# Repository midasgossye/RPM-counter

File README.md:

# RPM counter

## Repo structure

* [**Electronics:**](https://github.com/midasgossye/RPM-counter/tree/main/Electronics) Contains everything related to the Electronics, this includes the schematic (in pdf), KiCad files (schematic & PCB layout), PCB gerber files and a BOM (Bill Of Materials)
* [**Programming:**](https://github.com/midasgossye/RPM-counter/tree/main/Programming) Contains the Arduino source code
* [**CAD:**](https://github.com/midasgossye/RPM-counter/tree/main/CAD) Contains the 3D design files (Solidworks & STEP format) and STL files for 3D printing of the case
* [**images:**](https://github.com/midasgossye/RPM-counter/tree/main/images) Images of RPM counter

## Acknowledgements:

This project is mainly based on GreatScott's DIY RPM meter. Check out his awesome video where he explains the design process and working details of his DIY RPM meter/tachometer based on a cheap IR distance sensor module: [youtu.be/6QZMt4yyylU](https://youtu.be/6QZMt4yyylU)

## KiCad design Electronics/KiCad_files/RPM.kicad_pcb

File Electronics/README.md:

# RPM counter Electronics

This folder contains the schematic, BOM, KiCad files and gerber fabrication files for the PCB.

## Main features:

* ATMEGA328P Microcontroller with Arduino bootloader
* Built-in CH340 based USB <-> Serial
* Constant current IR LED driver
* Runs on single-cell LiPo
  * TP4560 based LiPo battery charger
  * LiPo protection circuitry
  * 3.3 V -> 5 V boost converter

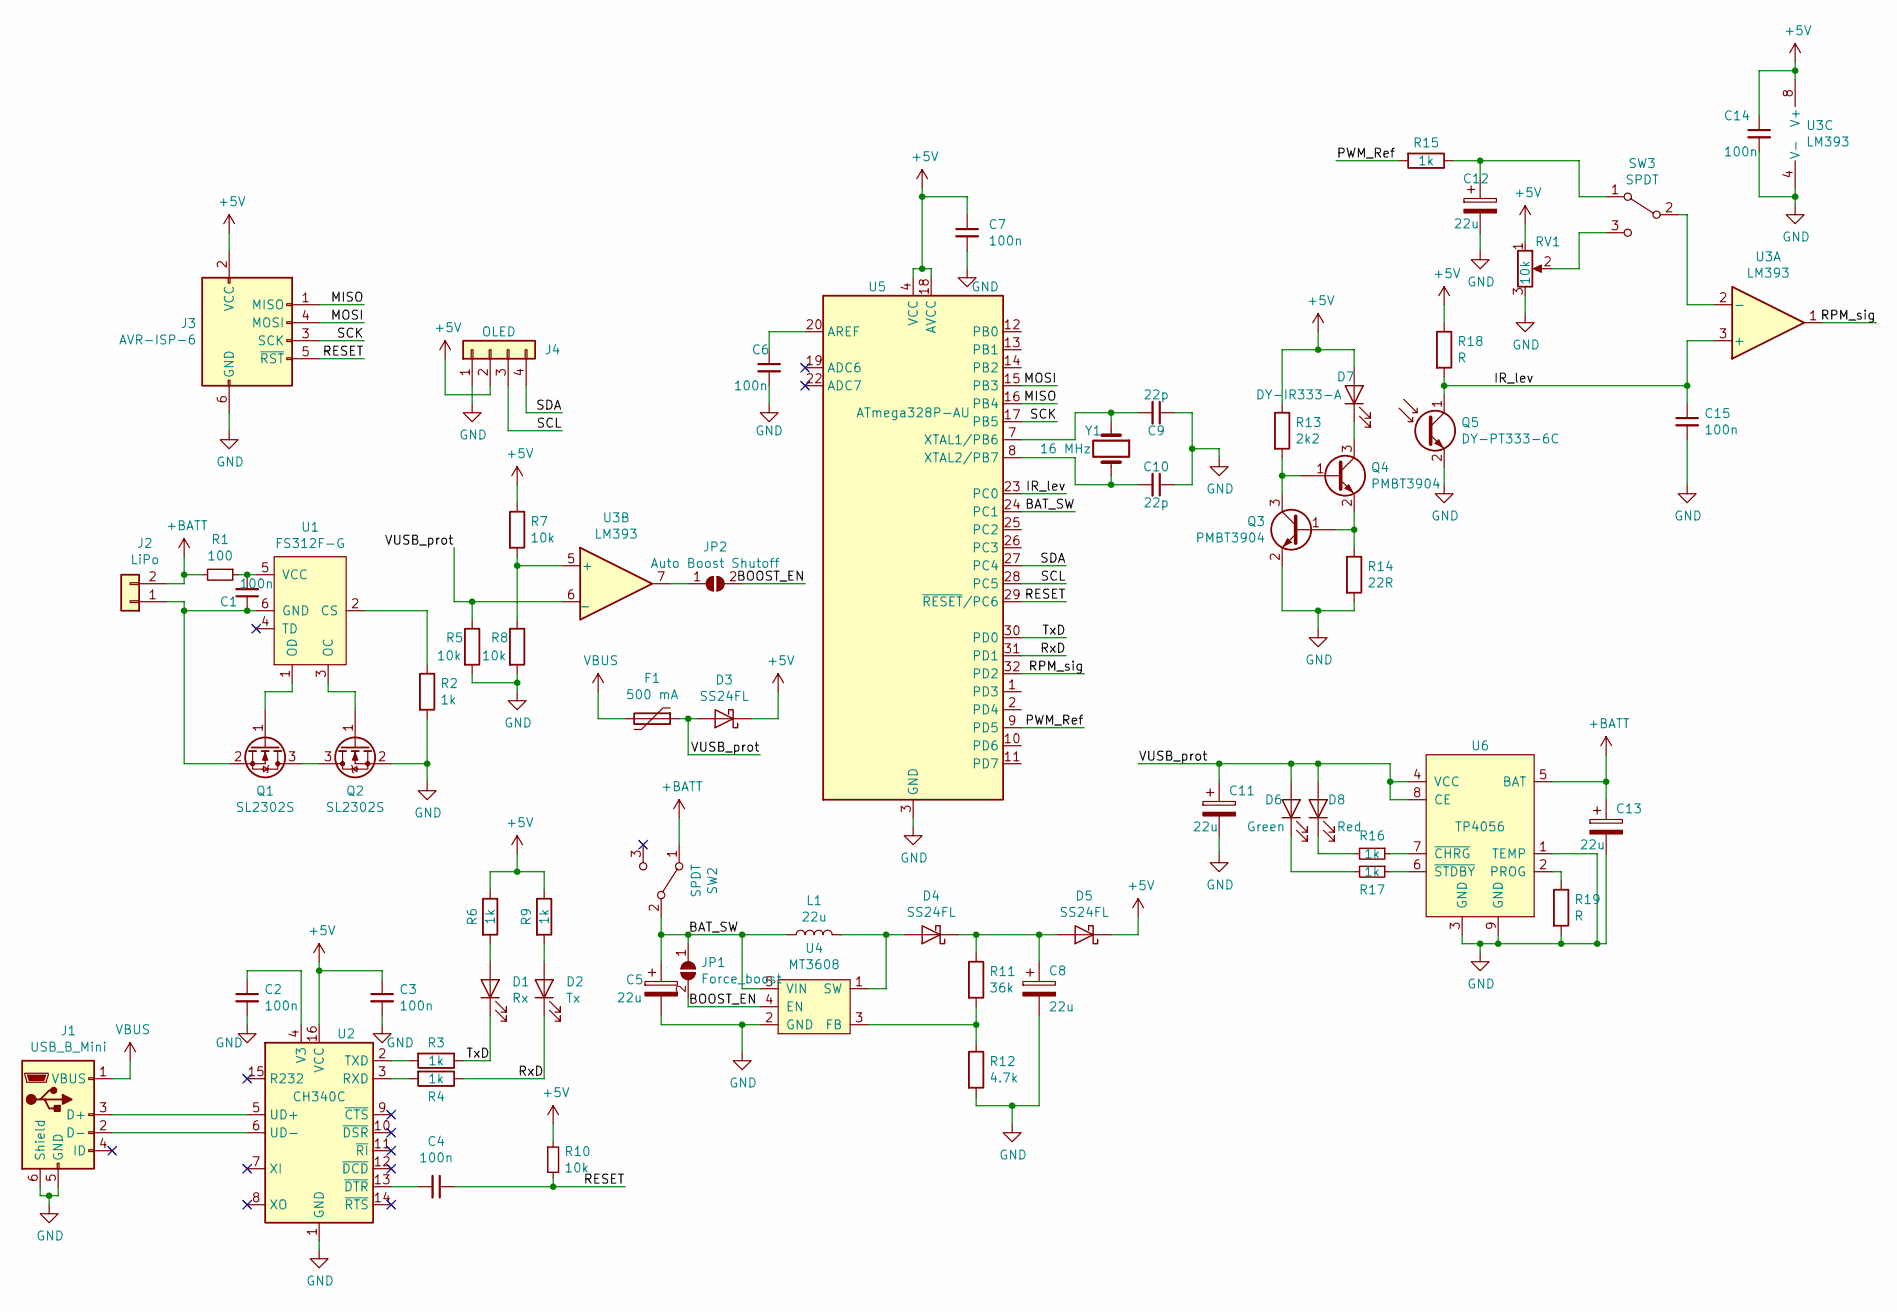
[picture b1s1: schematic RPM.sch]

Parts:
C1, C2, C3, C4, C6, C7, C14, C15: 100n; C_0603_1608Metric; MFR PART# 0603B104M250
C5, C8, C11, C12, C13: 22u; C_1206_3216Metric; MFR PART# CL31A226KOHNNNE
C9, C10: 22p; C_0805_2012Metric
D1: Rx; LED_0805_2012Metric
D2: Tx; LED_0805_2012Metric
D3, D4, D5: SS24FL; D_SOD-123; MFR PART# SS24FL
D6: Green; LED_0805_2012Metric
D7: DY-IR333-A; LED_D5.0mm_Horizontal_O1.27mm_Z3.0mm_IRGrey; MFR PART# DY-IR333-A
D8: Red; LED_0805_2012Metric
F1: 500 mA; Fuse_0805_2012Metric; MFR PART# JK-SMD0805-020
J1: USB_B_Mini; C105424; MFR PART# C105424
J2: LiPo; JST_PH_B2B-PH-K_1x02_P2.00mm_Vertical
J3: AVR-ISP-6; PinHeader_2x03_P2.54mm_Vertical; MFR PART# 210-92-03GB01
J4: OLED; PinSocket_1x04_P2.54mm_Vertical
JP1: Force_boost; SolderJumper-2_P1.3mm_Open_RoundedPad1.0x1.5mm
JP2: Auto Boost Shutoff; SolderJumper-2_P1.3mm_Open_RoundedPad1.0x1.5mm
L1: 22u; SNR5040K-SERIES; MFR PART# SNR5040K-220M
Q1, Q2: SL2302S; SOT-23; MFR PART# SL2302S
Q3, Q4: PMBT3904; SOT-23; MFR PART# PMBT3904,215
Q5: DY-PT333-6C; LED_D5.0mm_Horizontal_O1.27mm_Z3.0mm_Clear; MFR PART# DY-PT333-6C
R1: 100; R_0805_2012Metric
R2, R3, R4, R6, R9, R15, R16, R17: 1k; R_0603_1608Metric; MFR PART# 0603WAF1001T5E
R5, R7, R8, R10: 10k; R_0603_1608Metric; MFR PART# RTT03103JTP
R11: 36k; R_0603_1608Metric
R12: 4.7k; R_0603_1608Metric
R13: 2k2; R_0805_2012Metric
R14: 22R; R_Axial_DIN0207_L6.3mm_D2.5mm_P10.16mm_Horizontal; MFR PART# MFR0W4F390JA50
R18, R19: R; R_0805_2012Metric
RV1: 10k; Potentiometer_Vishay_T73XX_Horizontal; MFR PART# 3362S-1-103
SW2, SW3: SPDT; SK12D07VG5; MFR PART# SK12D07VG5
U1: FS312F-G; SOT-23-6; MFR PART# FS312F-G
U2: CH340C; SOIC-16_3.9x9.9mm_P1.27mm; MFR PART# CH340C
U3: LM393; SOP-8_3.76x4.96mm_P1.27mm; MFR PART# LM393
U4: MT3608; SOT-23-6; MFR PART# MT3608
U5: ATmega328P-AU; TQFP-32_7x7mm_P0.8mm; MFR PART# ATMEGA328P-AU
U6: TP4056; TI_SO-PowerPAD-8_ThermalVias; MFR PART# TP4056
Y1: 16 MHz; Crystal_HC18-U_Vertical; MFR PART# X49SD16MSD2SC

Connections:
+5V: C3.1, C7.1, C14.1, D3.1 (K), D5.1 (K), D7.2 (A), J3.2 (VCC), J4.2, R6.1, R7.1, R9.1, R10.1, R13.1, R18.1, RV1.1, U2.16 (VCC), U3.8 (V+), U5.4 (VCC), U5.6 (VCC), U5.18 (AVCC)
+BATT: C13.1, J2.2, R1.2, SW2.1 (A), U6.5 (BAT)
/BAT_SW: C5.1, JP1.1 (A), L1.1, SW2.2 (B), U4.5 (VIN), U5.24 (PC1)
/BOOST_EN: JP1.2 (B), JP2.2 (B), U4.4 (EN)
/IR_lev: C15.1, Q5.1 (C), R18.2, U3.3 (+), U5.23 (PC0)
/MISO: J3.1 (MISO), U5.16 (PB4)
/MOSI: J3.4 (MOSI), U5.15 (PB3)
/PWM_Ref: R15.2, U5.9 (PD5)
/RESET: C4.1, J3.5 (~RST), R10.2, U5.29 (~RESET~/PC6)
/RPM_sig: U3.1, U5.32 (PD2)
/RxD: D2.1 (K), R4.1, U5.31 (PD1)
/SCK: J3.3 (SCK), U5.17 (PB5)
/SCL: J4.3, U5.28 (PC5)
/SDA: J4.4, U5.27 (PC4)
/TxD: D1.1 (K), R3.1, U5.30 (PD0)
/VUSB_prot: C11.1, D3.2 (A), D6.2 (A), D8.2 (A), F1.1, R5.1, U3.6 (_), U6.4 (VCC), U6.8 (CE)
GND: C2.2, C3.2, C5.2, C6.2, C7.2, C8.2, C9.1, C10.1, C11.2, C12.2, C13.2, C14.2, C15.2, J1.5 (GND), J1.6 (Shield), J3.6 (GND), J4.1, Q2.2 (S), Q3.2 (E), Q5.2 (E), R2.2, R5.2, R8.2, R12.2, R14.2, R19.2, RV1.3, U2.1 (GND), U3.4 (V-), U4.2 (GND), U5.3 (GND), U5.5 (GND), U5.21 (GND), U6.1 (TEMP), U6.3 (GND), U6.9 (GND)
unnamed: C1.1, J2.1, Q1.2 (S), U1.6 (GND)
unnamed: C1.2, R1.1, U1.5 (VCC)
unnamed: C2.1, U2.4 (V3)
unnamed: C4.2, U2.13 (~DTR)
unnamed: C6.1, U5.20 (AREF)
unnamed: C8.1, D4.1 (K), D5.2 (A), R11.1
unnamed: C9.2, U5.7 (XTAL1/PB6), Y1.1
unnamed: C10.2, U5.8 (XTAL2/PB7), Y1.2
unnamed: C12.1, R15.1, SW3.1 (A)
unnamed: D1.2 (A), R6.2
unnamed: D2.2 (A), R9.2
unnamed: D4.2 (A), L1.2, U4.1 (SW)
unnamed: D6.1 (K), R17.2
unnamed: D7.1 (K), Q4.3 (C)
unnamed: D8.1 (K), R16.2
unnamed: J1.2 (D-), U2.6 (UD-)
unnamed: J1.3 (D+), U2.5 (UD+)
unnamed: JP2.1 (A), U3.7
unnamed: Q1.1 (G), U1.1 (OD)
unnamed: Q1.3 (D), Q2.3 (D)
unnamed: Q2.1 (G), U1.3 (OC)
unnamed: Q3.1 (B), Q4.2 (E), R14.1
unnamed: Q3.3 (C), Q4.1 (B), R13.2
unnamed: R2.1, U1.2 (CS)
unnamed: R3.2, U2.2 (TXD)
unnamed: R4.2, U2.3 (RXD)
unnamed: R7.2, R8.1, U3.5 (+)
unnamed: R11.2, R12.1, U4.3 (FB)
unnamed: R16.1, U6.7 (~CHRG)
unnamed: R17.1, U6.6 (~STDBY)
unnamed: R19.1, U6.2 (PROG)
unnamed: RV1.2, SW3.3 (C)
unnamed: SW3.2 (B), U3.2 (-)
VBUS: F1.2, J1.1 (VBUS)

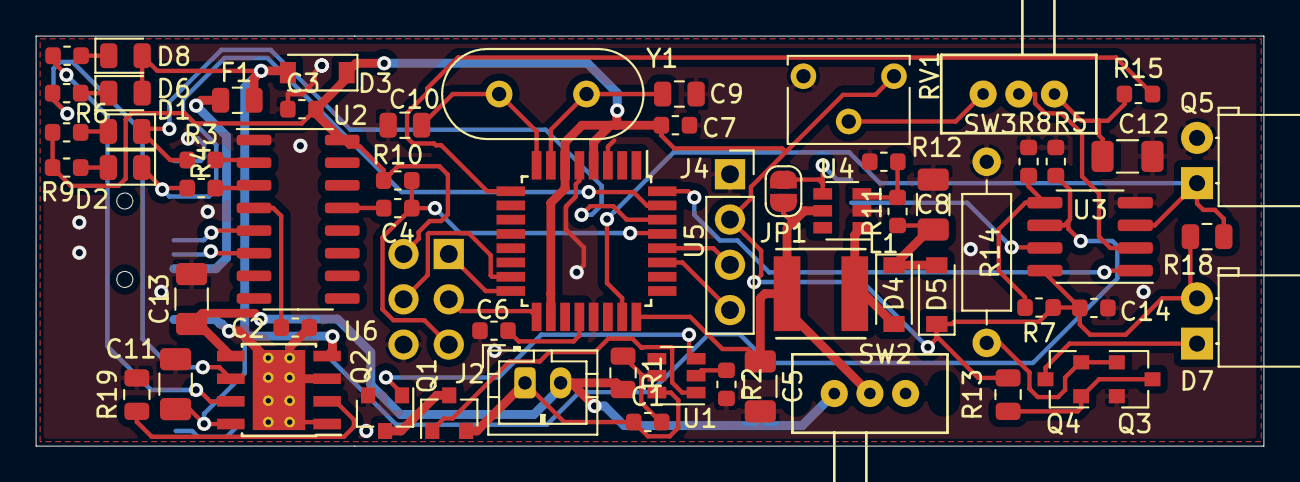
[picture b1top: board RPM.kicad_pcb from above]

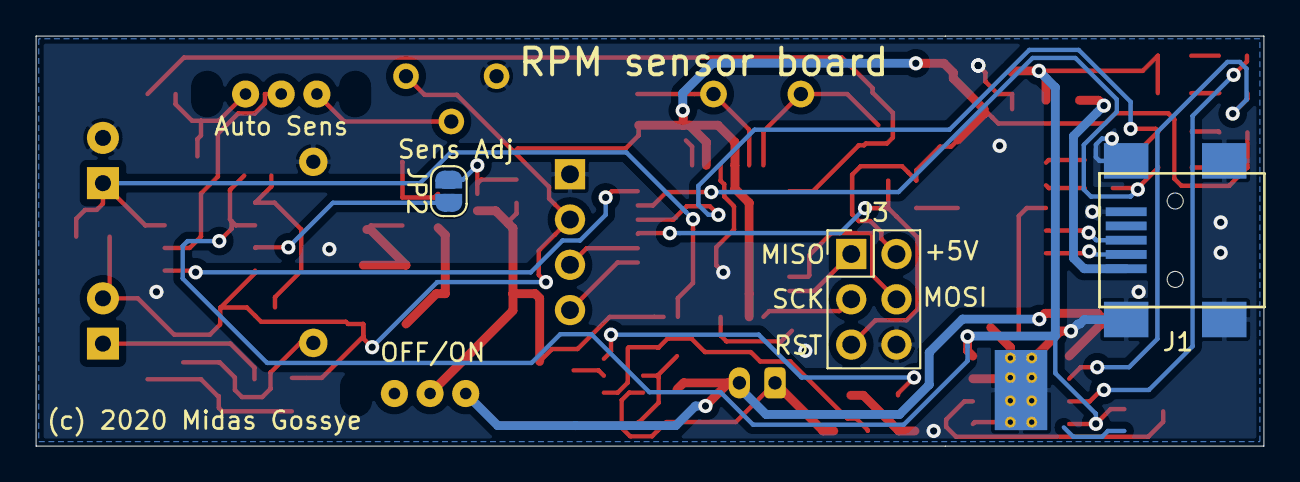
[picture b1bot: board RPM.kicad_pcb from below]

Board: 2 copper layers, 68.9 x 23.0 mm, 64 parts (3 on the bottom side), 51 nets.

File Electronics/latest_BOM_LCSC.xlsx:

Item | Qty | Reference(s) | Value | LibPart | Footprint | MFR PART#
1 | 7 | C1, C2, C3, C4, C6, C7, C14 | 100n | Device:C_Small | Capacitor_SMD:C_0603_1608Metric | 0603B104M250
2 | 5 | C5, C8, C11, C12, C13 | 22u | Device:CP | Capacitor_SMD:C_1206_3216Metric | CL31A226KOHNNNE
3 | 2 | C9, C10 | 22p | Device:C_Small | Capacitor_SMD:C_0805_2012Metric
4 | 1 | D1 | Rx | Device:LED | LED_SMD:LED_0805_2012Metric
5 | 1 | D2 | Tx | Device:LED | LED_SMD:LED_0805_2012Metric
6 | 3 | D3, D4, D5 | SS24FL | Device:D_Schottky | Diode_SMD:D_SOD-123 | SS24FL
7 | 1 | D6 | Green | Device:LED | LED_SMD:LED_0805_2012Metric
8 | 1 | D7 | DY-IR333-A | Device:LED | LED_THT:LED_D5.0mm_Horizontal_O1.27mm_Z3.0mm_IRGrey | DY-IR333-A
9 | 1 | D8 | Red | Device:LED | LED_SMD:LED_0805_2012Metric
10 | 1 | F1 | 500 mA | Device:Polyfuse | Fuse:Fuse_0805_2012Metric | JK-SMD0805-020
11 | 1 | J1 | USB_B_Mini | Connector:USB_B_Mini | SMD_connectors:C105424 | C105424
12 | 1 | J2 | LiPo | Connector_Generic:Conn_01x02 | Connector_JST:JST_PH_B2B-PH-K_1x02_P2.00mm_Vertical
13 | 1 | J3 | AVR-ISP-6 | Connector:AVR-ISP-6 | Connector_PinHeader_2.54mm:PinHeader_2x03_P2.54mm_Vertical | 210-92-03GB01
14 | 1 | J4 | OLED | Connector_Generic:Conn_01x04 | Connector_PinSocket_2.54mm:PinSocket_1x04_P2.54mm_Vertical
15 | 1 | JP1 | Force_boost | Jumper:SolderJumper_2_Open | Jumper:SolderJumper-2_P1.3mm_Open_RoundedPad1.0x1.5mm
16 | 1 | JP2 | Auto Boost Shutoff | Jumper:SolderJumper_2_Open | Jumper:SolderJumper-2_P1.3mm_Open_RoundedPad1.0x1.5mm
17 | 1 | L1 | 22u | Device:L | SMD_inductors:SNR5040K-SERIES | SNR5040K-220M
18 | 2 | Q1, Q2 | SL2302S | Device:Q_NMOS_GSD | Package_TO_SOT_SMD:SOT-23 | SL2302S
19 | 2 | Q3, Q4 | PMBT3904 | Device:Q_NPN_BEC | Package_TO_SOT_SMD:SOT-23 | PMBT3904,215
20 | 1 | Q5 | DY-PT333-6C | Device:Q_Photo_NPN_CE | LED_THT:LED_D5.0mm_Horizontal_O1.27mm_Z3.0mm_Clear | DY-PT333-6C
21 | 1 | R1 | 100 | Device:R_Small | Resistor_SMD:R_0805_2012Metric
22 | 6 | R2, R3, R4, R6, R9, R15 | 1k | Device:R | Resistor_SMD:R_0603_1608Metric | 0603WAF1001T5E
23 | 3 | R5, R7, R8 | 10k | Device:R | Resistor_SMD:R_0603_1608Metric
24 | 1 | R10 | 10k | Device:R_Small | Resistor_SMD:R_0603_1608Metric
25 | 1 | R11 | 36k | Device:R | Resistor_SMD:R_0603_1608Metric
26 | 1 | R12 | 4.7k | Device:R | Resistor_SMD:R_0603_1608Metric
27 | 1 | R13 | 2k2 | Device:R | Resistor_SMD:R_0805_2012Metric
28 | 1 | R14 | 39R | Device:R | Resistor_THT:R_Axial_DIN0207_L6.3mm_D2.5mm_P10.16mm_Horizontal | MFR0W4F390JA50
29 | 2 | R16, R17 | 1k | Device:R_Small | Resistor_SMD:R_0603_1608Metric | 0603WAF1001T5E
30 | 2 | R18, R19 | R | Device:R | Resistor_SMD:R_0805_2012Metric
31 | 1 | RV1 | 10k | Device:R_POT | Potentiometer_THT:Potentiometer_Vishay_T73XX_Horizontal | 3362S-1-103
32 | 2 | SW2, SW3 | SPDT | Switch:SW_SPDT | SMD_switches:SK12D07VG5 | SK12D07VG5
33 | 1 | U1 | FS312F-G | Battery_charger:FS312F-G | Package_TO_SOT_SMD:SOT-23-6 | FS312F-G
34 | 1 | U2 | CH340C | Interface_USB:CH340G | Package_SO:SOIC-16_3.9x9.9mm_P1.27mm | CH340C
35 | 1 | U3 | LM393 | Comparator:LM393 | Package_SO:SOP-8_3.76x4.96mm_P1.27mm | LM393
36 | 1 | U4 | MT3608 | Boost_converter:MT3608 | Package_TO_SOT_SMD:SOT-23-6 | MT3608
37 | 1 | U5 | ATmega328P-AU | MCU_Microchip_ATmega:ATmega328P-AU | Package_QFP:TQFP-32_7x7mm_P0.8mm | ATMEGA328P-AU
38 | 1 | U6 | TP4056 | Battery_charger:TP4056 | Package_SO:TI_SO-PowerPAD-8_ThermalVias | TP4056
39 | 1 | Y1 | 16 MHz | Device:Crystal | Crystal:Crystal_HC18-U_Vertical | X49SD16MSD2SC

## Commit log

2021-04-04 Added image
2021-04-04 added PCB design files
2021-04-04 added CAD
2021-04-04 Added CAD README
2021-04-04 Added Arduino code
2021-04-04 Added link to programming
2021-04-04 Added code README
2021-04-04 Added images
2021-04-04 Added images README

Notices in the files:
Electronics/KiCad_files/RPM.kicad_pcb:
(c) 2020 Midas Gossye
